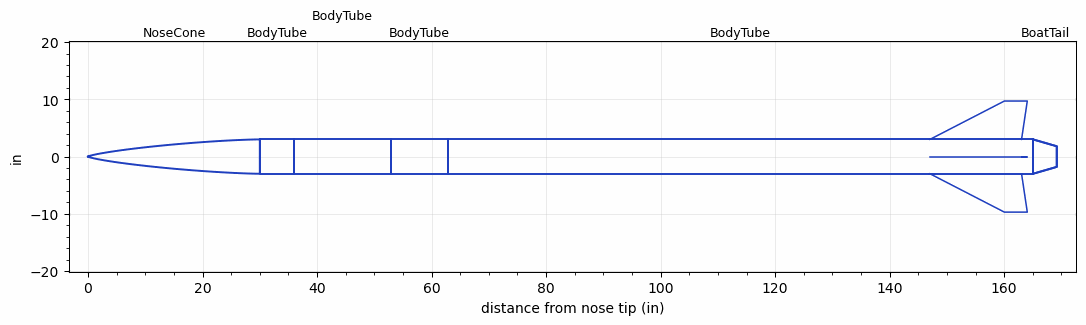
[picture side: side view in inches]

<RASAeroDocument>
 <FileVersion>2</FileVersion>
 <RocketDesign>
  <NoseCone>
   <Length>29.9999</Length>
   <Diameter>6</Diameter>
   <Shape>Von Karman Ogive</Shape>
   <Location>0</Location>
  </NoseCone>
  <BodyTube>
   <Length>6</Length>
   <Diameter>6</Diameter>
   <Location>29.9999</Location>
  </BodyTube>
  <BodyTube>
   <Length>16.828</Length>
   <Diameter>6</Diameter>
   <Location>35.9999</Location>
  </BodyTube>
  <BodyTube>
   <Length>10</Length>
   <Diameter>6</Diameter>
   <Location>52.8279</Location>
  </BodyTube>
  <BodyTube>
   <Length>102.1998</Length>
   <Diameter>6</Diameter>
   <Location>62.8279</Location>
   <BoattailLength>4.15</BoattailLength>
   <BoattailRearDiameter>3.6</BoattailRearDiameter>
   <Fin>
    <Count>4</Count>
    <Chord>16</Chord>
    <Span>6.7</Span>
    <SweepDistance>13</SweepDistance>
    <TipChord>4</TipChord>
    <Thickness>0.3</Thickness>
    <LERadius>0.06</LERadius>
    <Location>18</Location>
    <AirfoilSection>Double Wedge</AirfoilSection>
    <FX1>5</FX1>
   </Fin>
  </BodyTube>
  <BoatTail>
   <Length>4.15</Length>
   <Diameter>6</Diameter>
   <RearDiameter>3.6</RearDiameter>
   <Location>165.0277</Location>
  </BoatTail>
  <Surface>Camouflage Paint</Surface>
  <ModifiedBarrowman>True</ModifiedBarrowman>
  <Turbulence>True</Turbulence>
  <UseBooster1>False</UseBooster1>
  <UseBooster2>False</UseBooster2>
  <Comments>2027 IREC Rocket Design</Comments>
 </RocketDesign>
 <LaunchSite>
  <Altitude>2950</Altitude>
  <Pressure>29.83</Pressure>
  <RodAngle>4</RodAngle>
  <RodLength>32.8</RodLength>
  <Temperature>92.19</Temperature>
  <WindSpeed>11.46</WindSpeed>
 </LaunchSite>
 <Recovery>
  <Altitude1>0</Altitude1>
  <Altitude2>0</Altitude2>
  <DeviceType1>None</DeviceType1>
  <DeviceType2>None</DeviceType2>
  <Event1>False</Event1>
  <Event2>False</Event2>
  <Size1>0</Size1>
  <Size2>0</Size2>
  <EventType1>None</EventType1>
  <EventType2>None</EventType2>
  <CD1>0</CD1>
  <CD2>0</CD2>
 </Recovery>
 <SimulationList>
  <Simulation>
   <SustainerEngine>PER_MY_LAST-eng  (TAMUSRT)</SustainerEngine>
   <SustainerLaunchWt>145.19</SustainerLaunchWt>
   <SustainerCG>98.83</SustainerCG>
   <SustainerIgnitionDelay>0</SustainerIgnitionDelay>
   <Booster1SeparationDelay>0</Booster1SeparationDelay>
   <Booster1IgnitionDelay>0</Booster1IgnitionDelay>
   <IncludeBooster1>False</IncludeBooster1>
   <Booster2Delay>0</Booster2Delay>
   <IncludeBooster2>False</IncludeBooster2>
   <TimetoApogee>45.59835</TimetoApogee>
   <MaxAltitude>32198.79</MaxAltitude>
   <MaxVelocity>1624.603</MaxVelocity>
  </Simulation>
  <Simulation>
   <SustainerLaunchWt>145.1851</SustainerLaunchWt>
   <SustainerCG>98.4516</SustainerCG>
   <SustainerIgnitionDelay>0</SustainerIgnitionDelay>
   <Booster1SeparationDelay>0</Booster1SeparationDelay>
   <Booster1IgnitionDelay>0</Booster1IgnitionDelay>
   <IncludeBooster1>False</IncludeBooster1>
   <Booster2Delay>0</Booster2Delay>
   <IncludeBooster2>False</IncludeBooster2>
  </Simulation>
  <Simulation>
   <SustainerLaunchWt>145.1851</SustainerLaunchWt>
   <SustainerCG>98.4516</SustainerCG>
   <SustainerIgnitionDelay>0</SustainerIgnitionDelay>
   <Booster1SeparationDelay>0</Booster1SeparationDelay>
   <Booster1IgnitionDelay>0</Booster1IgnitionDelay>
   <IncludeBooster1>False</IncludeBooster1>
   <Booster2Delay>0</Booster2Delay>
   <IncludeBooster2>False</IncludeBooster2>
  </Simulation>
 </SimulationList>
</RASAeroDocument>
